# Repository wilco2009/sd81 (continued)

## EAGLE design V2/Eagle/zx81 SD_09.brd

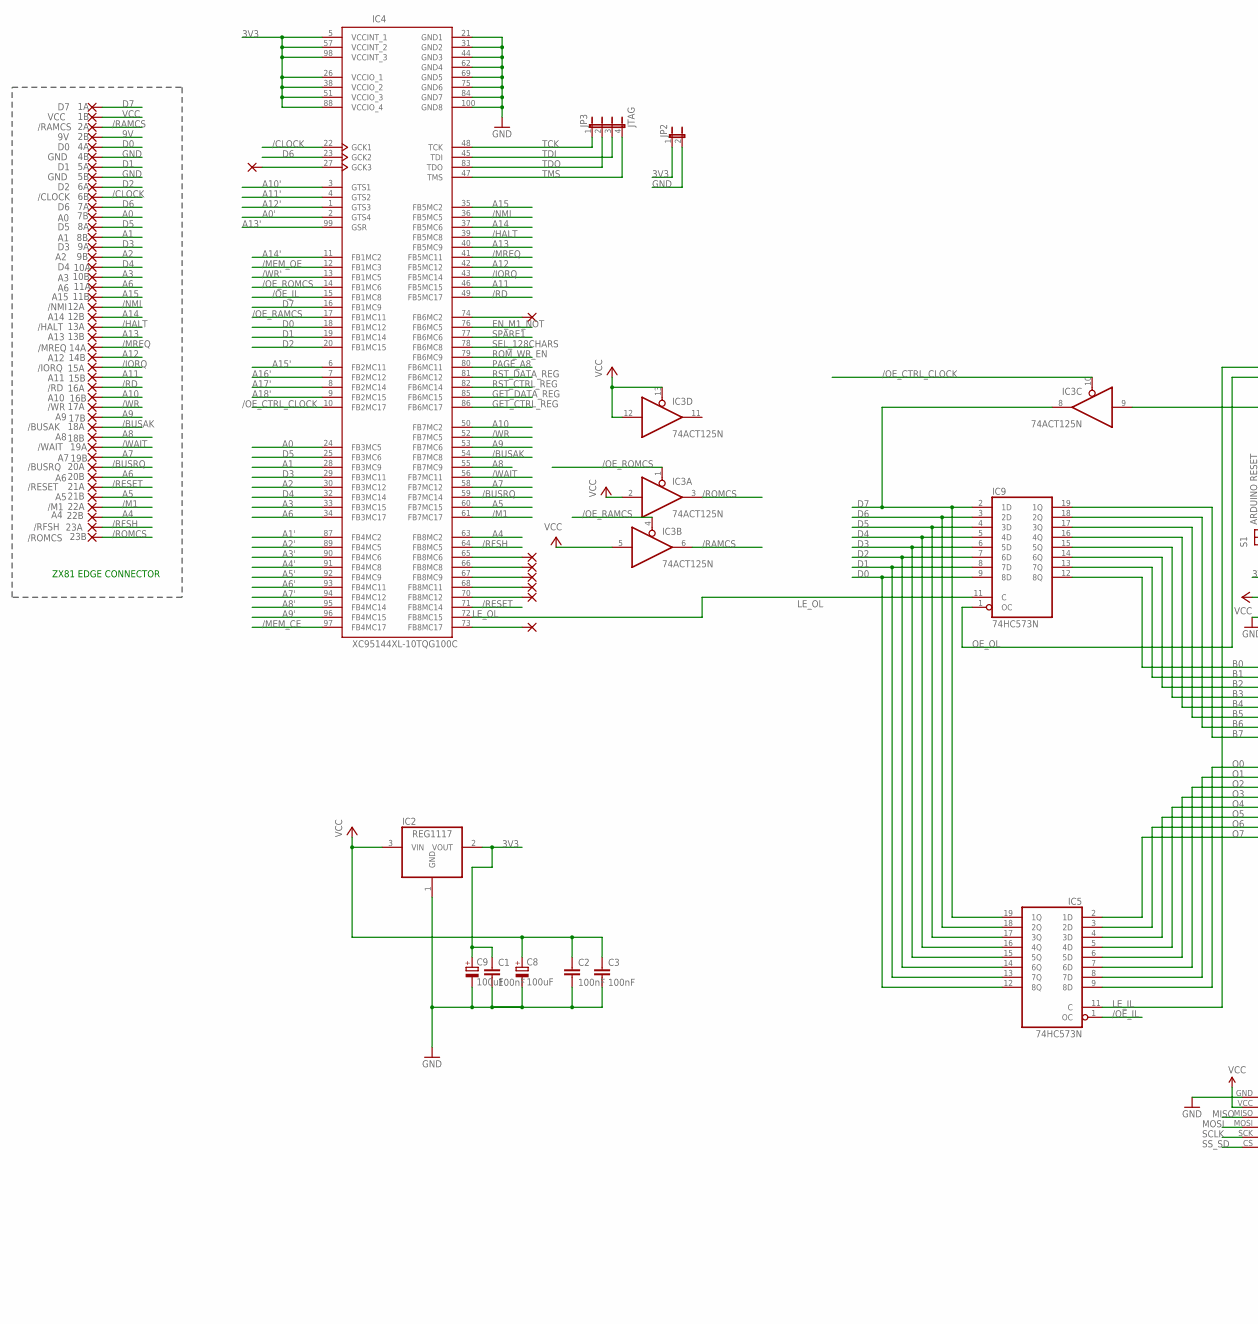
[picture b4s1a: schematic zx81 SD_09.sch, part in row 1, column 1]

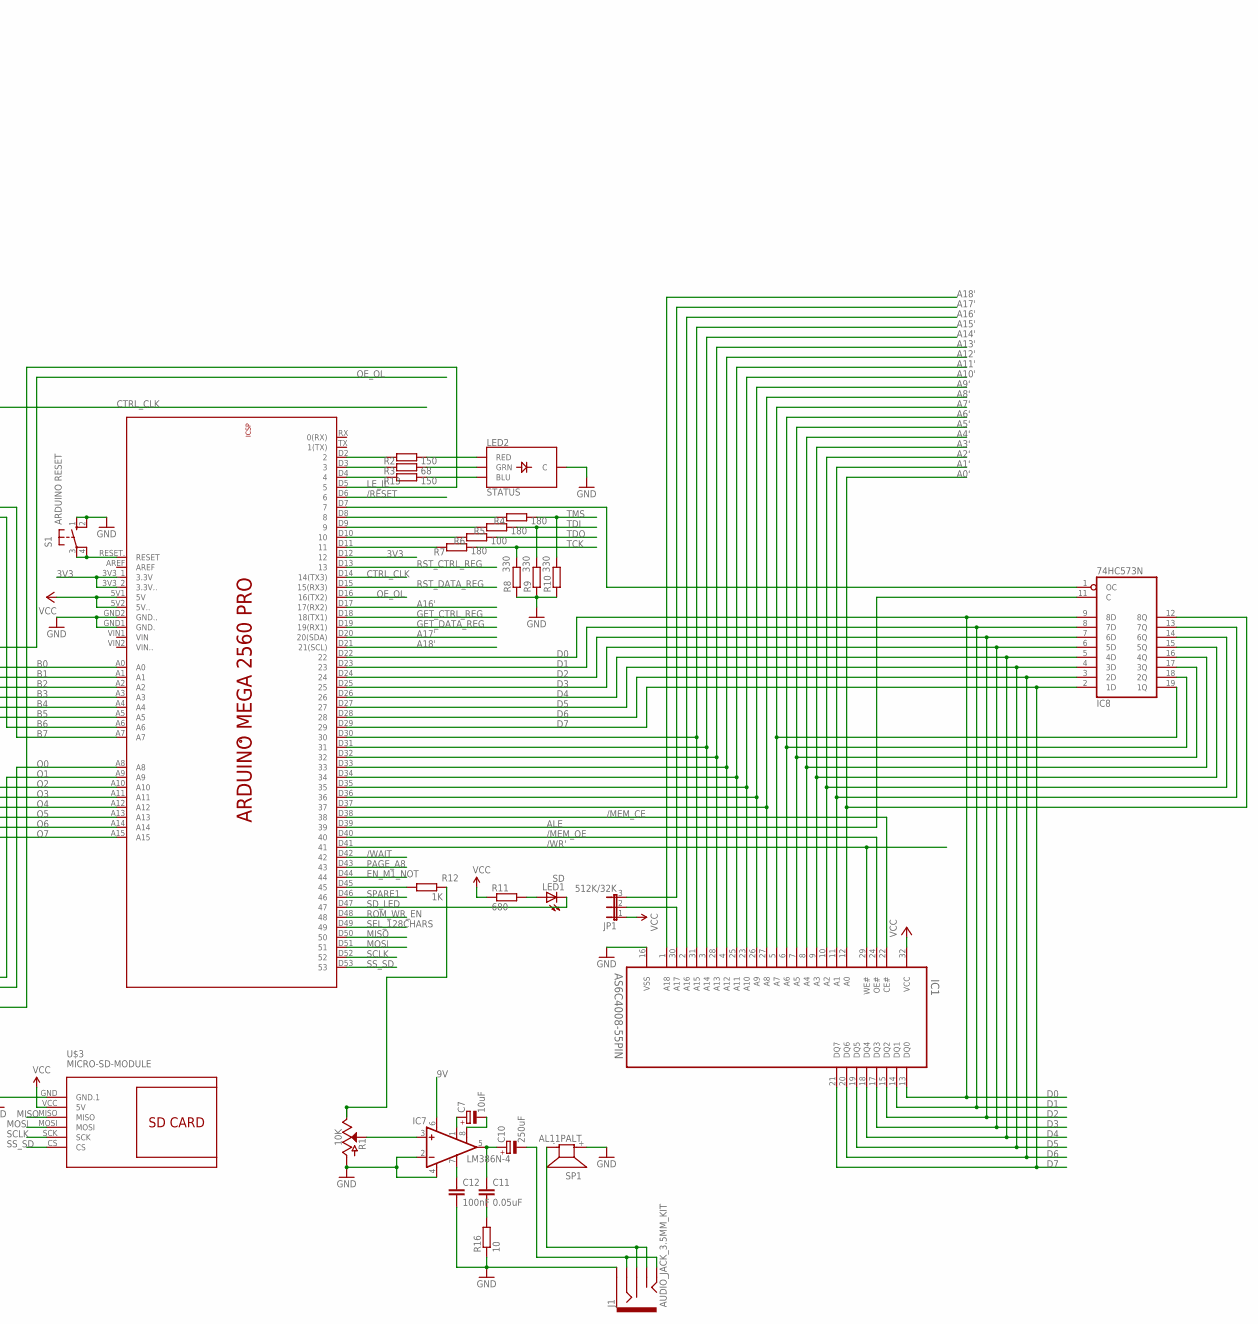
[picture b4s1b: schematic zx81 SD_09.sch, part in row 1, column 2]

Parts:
1A: D7; EDGEPIN
1B: VCC; EDGEPIN
2A: /RAMCS; EDGEPIN
2B: 9V; EDGEPIN
4A: D0; EDGEPIN
4B, 5B: GND; EDGEPIN
5A: D1; EDGEPIN
6A: D2; EDGEPIN
6B: /CLOCK; EDGEPIN
7A: D6; EDGEPIN
7B: A0; EDGEPIN
8A: D5; EDGEPIN
8B: A1; EDGEPIN
9A: D3; EDGEPIN
9B: A2; EDGEPIN
10A: D4; EDGEPIN
10B: A3; EDGEPIN
11A, 20B: A6; EDGEPIN
11B: A15; EDGEPIN
12A: /NMI; EDGEPIN
12B: A14; EDGEPIN
13A: /HALT; EDGEPIN
13B: A13; EDGEPIN
14A: /MREQ; EDGEPIN
14B: A12; EDGEPIN
15A: /IORQ; EDGEPIN
15B: A11; EDGEPIN
16A: /RD; EDGEPIN
16B: A10; EDGEPIN
17A: /WR; EDGEPIN
17B: A9; EDGEPIN
18A: /BUSAK; EDGEPIN
18B: A8; EDGEPIN
19A: /WAIT; EDGEPIN
19B: A7; EDGEPIN
20A: /BUSRQ; EDGEPIN
21A: /RESET; EDGEPIN
21B: A5; EDGEPIN
22A: /M1; EDGEPIN
22B: A4; EDGEPIN
23A: /RFSH; EDGEPIN
23B: /ROMCS; EDGEPIN
C1, C2, C3, C12: 100nF; C025-040X050
C7: 10uF; E2-5
C8, C9: 100uF; E2-5
C10: 250uF; E2-5
C11: 0.05uF; C025-040X050
IC1: AS6C4008-55PIN; DIP1524W45P254L4203H406Q32
IC2: REG1117; SOT223
IC3: 74ACT125N; DIL14
IC4: XC95144XL-10TQG100C; TQFP100
IC5, IC8, IC9: 74HC573N; DIL20
IC7: LM386N-4; DIL08
J1: AUDIO_JACK_3.5MM_KIT; AUDIO-JACK-KIT
JP1: 512K/32K; JP2
JP2: JP1E; JP1
JP3: JTAG; JP4
LED1: SD; LED5MM
LED2: STATUS; LED-RGB-THRU
PAD1, PAD2, PAD3, PAD4, PAD5, PAD6, PAD7, PAD8: 1,6/0,8
R1: 10K; POT-WHEEL
R2, R13: 150; 0204/7
R3: 68; 0204/7
R4, R5, R7: 180; 0204/7
R6: 100; 0204/7
R8, R9, R10: 330; 0204/7
R11: 680; 0204/7
R12: 1K; 0204/7
R16: 10; 0204/7
S1: ARDUINO RESET; B3F-10XX
SP1: AL11PALT; ALT
U$2: ARDUINO_MEGA2560_PRO
U$3: MICRO-SD-MODULE; MICROSD-MODULE

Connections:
3V3: C1.1, C9.+, IC2.2 (VOUT), IC4.5 (VCCINT_1), IC4.26 (VCCIO_1), IC4.38 (VCCIO_2), IC4.51 (VCCIO_3), IC4.57 (VCCINT_2), IC4.88 (VCCIO_4), IC4.98 (VCCINT_3), JP2.1, U$2.3V3_1 (3.3V), U$2.3V3_2 (3.3V..), U$2.D12 (12)
9V: 2B.1, IC7.6 (VS)
/BUSAK: 18A.1, IC4.54 (FB7MC8)
/BUSRQ: 20A.1, IC4.59 (FB7MC14)
/CLOCK: 6B.1, IC4.22 (GCK1)
/HALT: 13A.1, IC4.39 (FB5MC8)
/IORQ: 15A.1, IC4.43 (FB5MC14)
/M1: 22A.1, IC4.61 (FB7MC17)
/MEM_CE: IC1.22 (CE#), IC4.97 (FB4MC17), U$2.D38 (38)
/MEM_OE: IC1.24 (OE#), IC4.12 (FB1MC3), U$2.D40 (40)
/MREQ: 14A.1, IC4.41 (FB5MC11)
/NMI: 12A.1, IC4.36 (FB5MC5)
/OE_CTRL_CLOCK: IC3.10 (OE), IC4.10 (FB2MC17)
/OE_IL: IC4.15 (FB1MC8), IC5.1 (OC)
/OE_RAMCS: IC3.4 (OE), IC4.17 (FB1MC11)
/OE_ROMCS: IC3.1 (OE), IC4.14 (FB1MC6)
/RAMCS: 2A.1, IC3.6 (O)
/RD: 16A.1, IC4.49 (FB5MC17)
/RESET: 21A.1, IC4.71 (FB8MC14), U$2.D6 (6)
/RFSH: 23A.1, IC4.64 (FB8MC5)
/ROMCS: 23B.1, IC3.3 (O)
/WAIT: 19A.1, IC4.56 (FB7MC11), U$2.D42 (42)
/WR: 17A.1, IC4.52 (FB7MC5)
/WR': IC1.29 (WE#), IC4.13 (FB1MC5), U$2.D41 (41)
A0: 7B.1, IC4.24 (FB3MC5)
A0': IC1.12 (A0), IC4.2 (GTS4), IC8.12 (8Q)
A1: 8B.1, IC4.28 (FB3MC9)
A1': IC1.11 (A1), IC4.87 (FB4MC2), IC8.13 (7Q)
A2: 9B.1, IC4.30 (FB3MC12)
A2': IC1.10 (A2), IC4.89 (FB4MC5), IC8.14 (6Q)
A3: 10B.1, IC4.33 (FB3MC15)
A3': IC1.9 (A3), IC4.90 (FB4MC6), IC8.15 (5Q)
A4: 22B.1, IC4.63 (FB8MC2)
A4': IC1.8 (A4), IC4.91 (FB4MC8), IC8.16 (4Q)
A5: 21B.1, IC4.60 (FB7MC15)
A5': IC1.7 (A5), IC4.92 (FB4MC9), IC8.17 (3Q)
A6: 11A.1, 20B.1, IC4.34 (FB3MC17)
A6': IC1.6 (A6), IC4.93 (FB4MC11), IC8.18 (2Q)
A7: 19B.1, IC4.58 (FB7MC12)
A7': IC1.5 (A7), IC4.94 (FB4MC12), IC8.19 (1Q)
A8: 18B.1, IC4.55 (FB7MC9)
A8': IC1.27 (A8), IC4.95 (FB4MC14), U$2.D37 (37)
A9: 17B.1, IC4.53 (FB7MC6)
A9': IC1.26 (A9), IC4.96 (FB4MC15), U$2.D36 (36)
A10: 16B.1, IC4.50 (FB7MC2)
A10': IC1.23 (A10), IC4.3 (GTS1), U$2.D35 (35)
A11: 15B.1, IC4.46 (FB5MC15)
A11': IC1.25 (A11), IC4.4 (GTS2), U$2.D34 (34)
A12: 14B.1, IC4.42 (FB5MC12)
A12': IC1.4 (A12), IC4.1 (GTS3), U$2.D33 (33)
A13: 13B.1, IC4.40 (FB5MC9)
A13': IC1.28 (A13), IC4.99 (GSR), U$2.D32 (32)
A14: 12B.1, IC4.37 (FB5MC6)
A14': IC1.3 (A14), IC4.11 (FB1MC2), U$2.D31 (31)
A15: 11B.1, IC4.35 (FB5MC2)
A15': IC1.31 (A15), IC4.6 (FB2MC11), U$2.D30 (30)
A16': IC1.2 (A16), IC4.7 (FB2MC12), U$2.D17 (17(RX2))
A17': IC4.8 (FB2MC14), JP1.3, U$2.D20 (20(SDA))
A18': IC1.1 (A18), IC4.9 (FB2MC15), U$2.D21 (21(SCL))
ALE: IC8.11 (C), U$2.D39 (39)
B0: IC9.19 (1Q), U$2.A7
B1: IC9.18 (2Q), U$2.A6
B2: IC9.17 (3Q), U$2.A5
B3: IC9.16 (4Q), U$2.A4
B4: IC9.15 (5Q), U$2.A3
B5: IC9.14 (6Q), U$2.A2
B6: IC9.13 (7Q), U$2.A1
B7: IC9.12 (8Q), U$2.A0
CTRL_CLK: IC3.9 (I), U$2.D14 (14(TX3))
D0: 4A.1, IC1.13 (DQ0), IC4.18 (FB1MC12), IC5.12 (8Q), IC8.9 (8D), IC9.9 (8D), U$2.D22 (22)
D1: 5A.1, IC1.14 (DQ1), IC4.19 (FB1MC14), IC5.13 (7Q), IC8.8 (7D), IC9.8 (7D), U$2.D23 (23)
D2: 6A.1, IC1.15 (DQ2), IC4.20 (FB1MC15), IC5.14 (6Q), IC8.7 (6D), IC9.7 (6D), U$2.D24 (24)
D3: 9A.1, IC1.17 (DQ3), IC4.29 (FB3MC11), IC5.15 (5Q), IC8.6 (5D), IC9.6 (5D), U$2.D25 (25)
D4: 10A.1, IC1.18 (DQ4), IC4.32 (FB3MC14), IC5.16 (4Q), IC8.5 (4D), IC9.5 (4D), U$2.D26 (26)
D5: 8A.1, IC1.19 (DQ5), IC4.25 (FB3MC6), IC5.17 (3Q), IC8.4 (3D), IC9.4 (3D), U$2.D27 (27)
D6: 7A.1, IC1.20 (DQ6), IC4.23 (GCK2), IC5.18 (2Q), IC8.3 (2D), IC9.3 (2D), U$2.D28 (28)
D7: 1A.1, IC1.21 (DQ7), IC3.8 (O), IC4.16 (FB1MC9), IC5.19 (1Q), IC8.2 (1D), IC9.2 (1D), U$2.D29 (29)
EN_M1_NOT: IC4.76 (FB6MC5), U$2.D44 (44)
GET_CTRL_REG: IC4.86 (FB6MC17), U$2.D18 (18(TX1))
GET_DATA_REG: IC4.85 (FB6MC15), U$2.D19 (19(RX1))
GND: 4B.1, 5B.1, C1.2, C2.2, C3.2, C8.-, C9.-, C12.2, IC1.16 (VSS), IC2.1 (GND), IC3.7 (GND), IC4.21 (GND1), IC4.31 (GND2), IC4.44 (GND3), IC4.62 (GND4), IC4.69 (GND5), IC4.75 (GND6), IC4.84 (GND7), IC4.100 (GND8), IC5.10 (GND), IC7.2 (-IN), IC7.4 (GND), IC8.10 (GND), IC9.10 (GND), J1.SLEEVE, JP2.2, LED2.2 (C), R1.P$1 (A), R8.1, R9.1, R10.1, R16.1, S1.1 (S), S1.2 (S1), SP1.+ (1), U$2.GND1 (GND.), U$2.GND2 (GND..), U$3.GND (GND.1)
LE_IL: IC5.11 (C), U$2.D5 (5)
LE_OL: IC4.72 (FB8MC15), IC9.11 (C)
MISO: U$2.D50 (50), U$3.MISO
MOSI: U$2.D51 (51), U$3.MOSI
unnamed: IC8.1 (OC), U$2.D7 (7)
unnamed: IC4.74 (FB6MC2), PAD8.1
unnamed: IC1.30 (A17), JP1.2
unnamed: J1.RSH, J1.TSH, SP1.- (2)
unnamed: R4.1, U$2.D8 (8)
unnamed: C10.-, J1.RING, J1.TIP
unnamed: IC7.3 (+IN), R1.P$3 (S)
unnamed: R1.P$2 (E), R12.2
unnamed: R12.1, U$2.D45 (45)
unnamed: C7.+, IC7.1 (GAIN)
unnamed: IC4.65 (FB8MC6), PAD2.1
unnamed: R5.1, U$2.D9 (9)
unnamed: R6.1, U$2.D10 (10)
unnamed: R7.1, U$2.D11 (11)
unnamed: LED1.A, R11.2
unnamed: IC4.66 (FB8MC8), PAD3.1
unnamed: C7.-, IC7.8 (GAIN)
unnamed: C10.+, C11.1, IC7.5 (OUT)
unnamed: IC4.67 (FB8MC9), PAD4.1
unnamed: C12.1, IC7.7 (BYPASS)
unnamed: C11.2, R16.2
unnamed: IC4.68 (FB8MC11), PAD5.1
unnamed: IC4.73 (FB8MC17), PAD6.1
unnamed: IC4.27 (GCK3), PAD1.1
unnamed: IC4.70 (FB8MC12), PAD7.1
unnamed: LED2.1 (RED), R2.2
unnamed: LED2.4 (GRN), R3.2
unnamed: LED2.3 (BLU), R13.2
unnamed: R2.1, U$2.D2 (2)
unnamed: R3.1, U$2.D3 (3)
unnamed: R13.1, U$2.D4 (4)
unnamed: S1.3, S1.4 (P1), U$2.RESET. (RESET)
O0: IC5.2 (1D), U$2.A15
O1: IC5.3 (2D), U$2.A14
O2: IC5.4 (3D), U$2.A13
O3: IC5.5 (4D), U$2.A12
O4: IC5.6 (5D), U$2.A11
O5: IC5.7 (6D), U$2.A10
O6: IC5.8 (7D), U$2.A9
O7: IC5.9 (8D), U$2.A8
OE_OL: IC9.1 (OC), U$2.D16 (16(TX2))
PAGE_A8: IC4.80 (FB6MC11), U$2.D43 (43)
ROM_WR_EN: IC4.79 (FB6MC9), U$2.D48 (48)
RST_CTRL_REG: IC4.82 (FB6MC14), U$2.D13 (13)
RST_DATA_REG: IC4.81 (FB6MC12), U$2.D15 (15(RX3))
SCLK: U$2.D52 (52), U$3.SCK
SD_LED: LED1.K (C), U$2.D47 (47)
SEL_128CHARS: IC4.78 (FB6MC8), U$2.D49 (49)
SPARE1: IC4.77 (FB6MC6), U$2.D46 (46)
SS_SD: U$2.D53 (53), U$3.CS
TCK: IC4.48 (TCK), JP3.1, R7.2, R8.2
TDI: IC4.45 (TDI), JP3.3, R5.2, R9.2
TDO: IC4.83 (TDO), JP3.2, R6.2
TMS: IC4.47 (TMS), JP3.4, R4.2, R10.2
VCC: 1B.1, C2.1, C3.1, C8.+, IC1.32 (VCC), IC2.3 (VIN), IC3.2 (I), IC3.5 (I), IC3.12 (I), IC3.13 (OE), IC3.14 (VCC), IC5.20 (VCC), IC8.20 (VCC), IC9.20 (VCC), JP1.1, R11.1, U$2.5V1 (5V), U$2.5V2 (5V..), U$3.VCC (5V)

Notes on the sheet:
ZX81 EDGE CONNECTOR

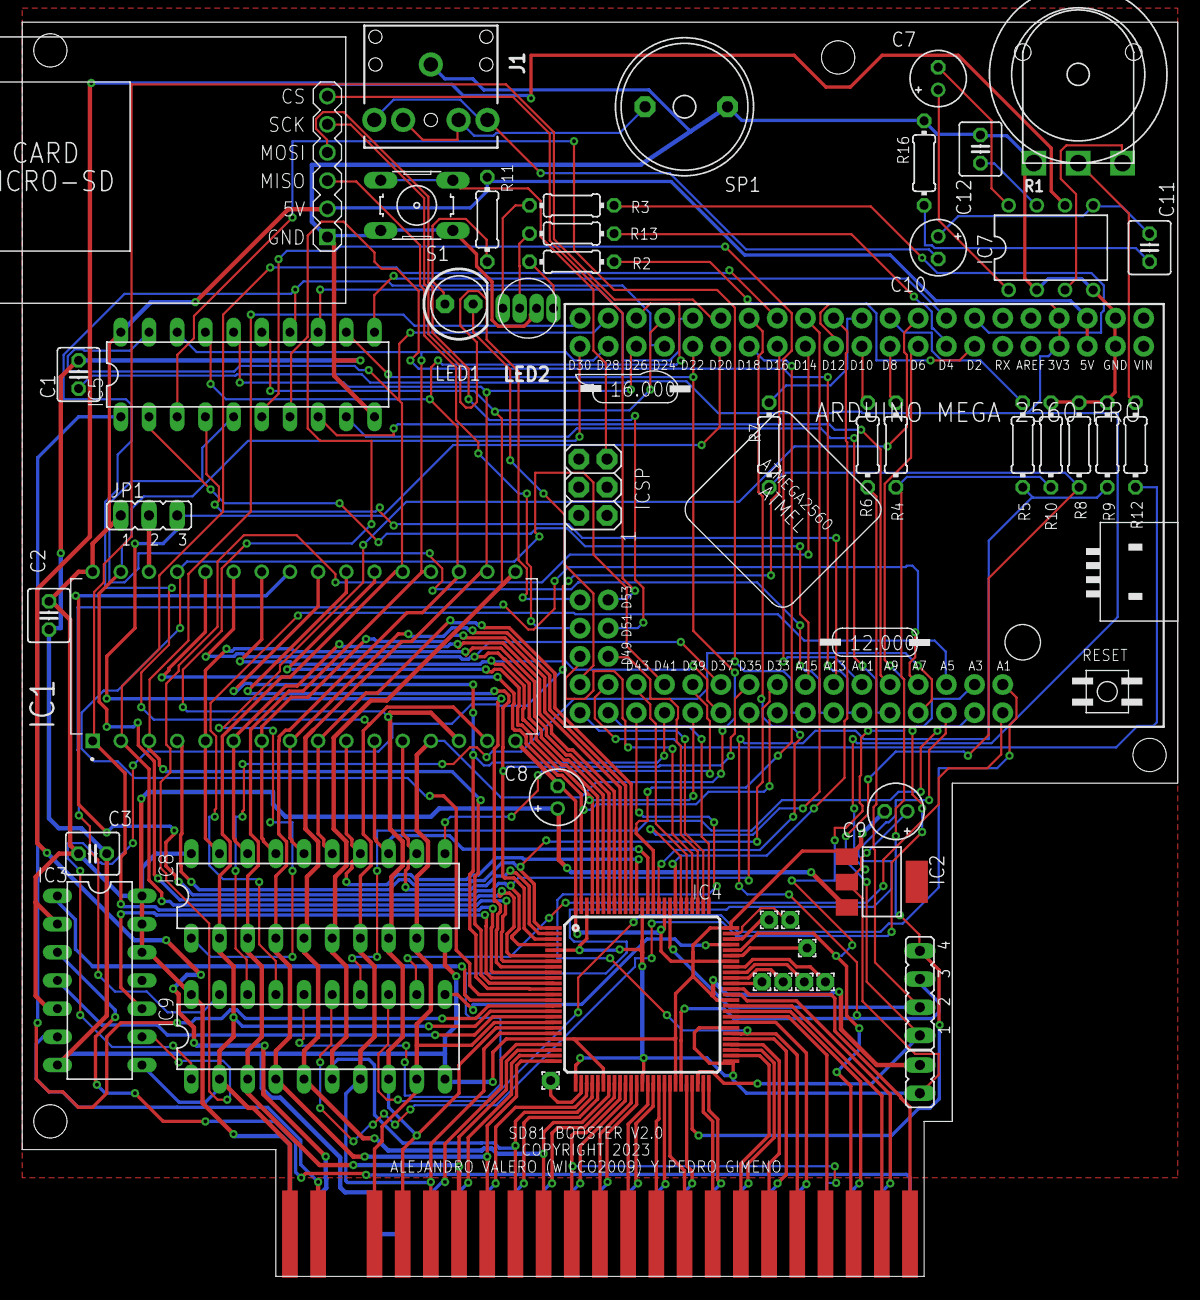
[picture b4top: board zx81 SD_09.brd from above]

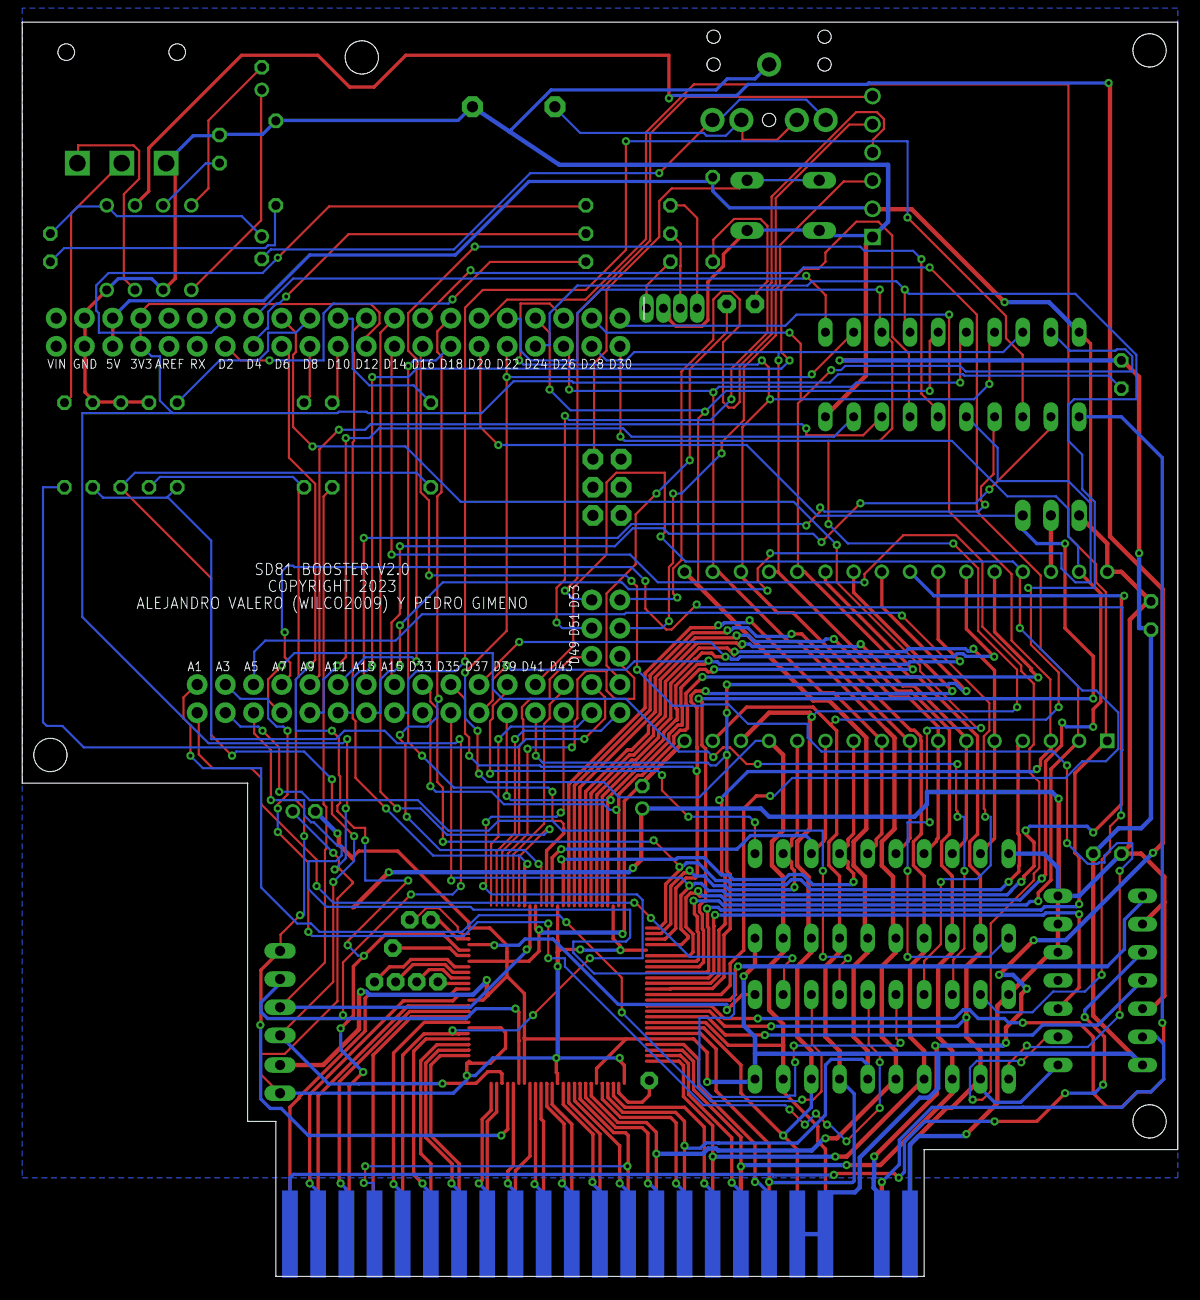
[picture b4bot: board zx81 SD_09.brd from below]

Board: 2 copper layers, 104.1 x 113.0 mm, 93 parts (22 on the bottom side), 140 nets.
